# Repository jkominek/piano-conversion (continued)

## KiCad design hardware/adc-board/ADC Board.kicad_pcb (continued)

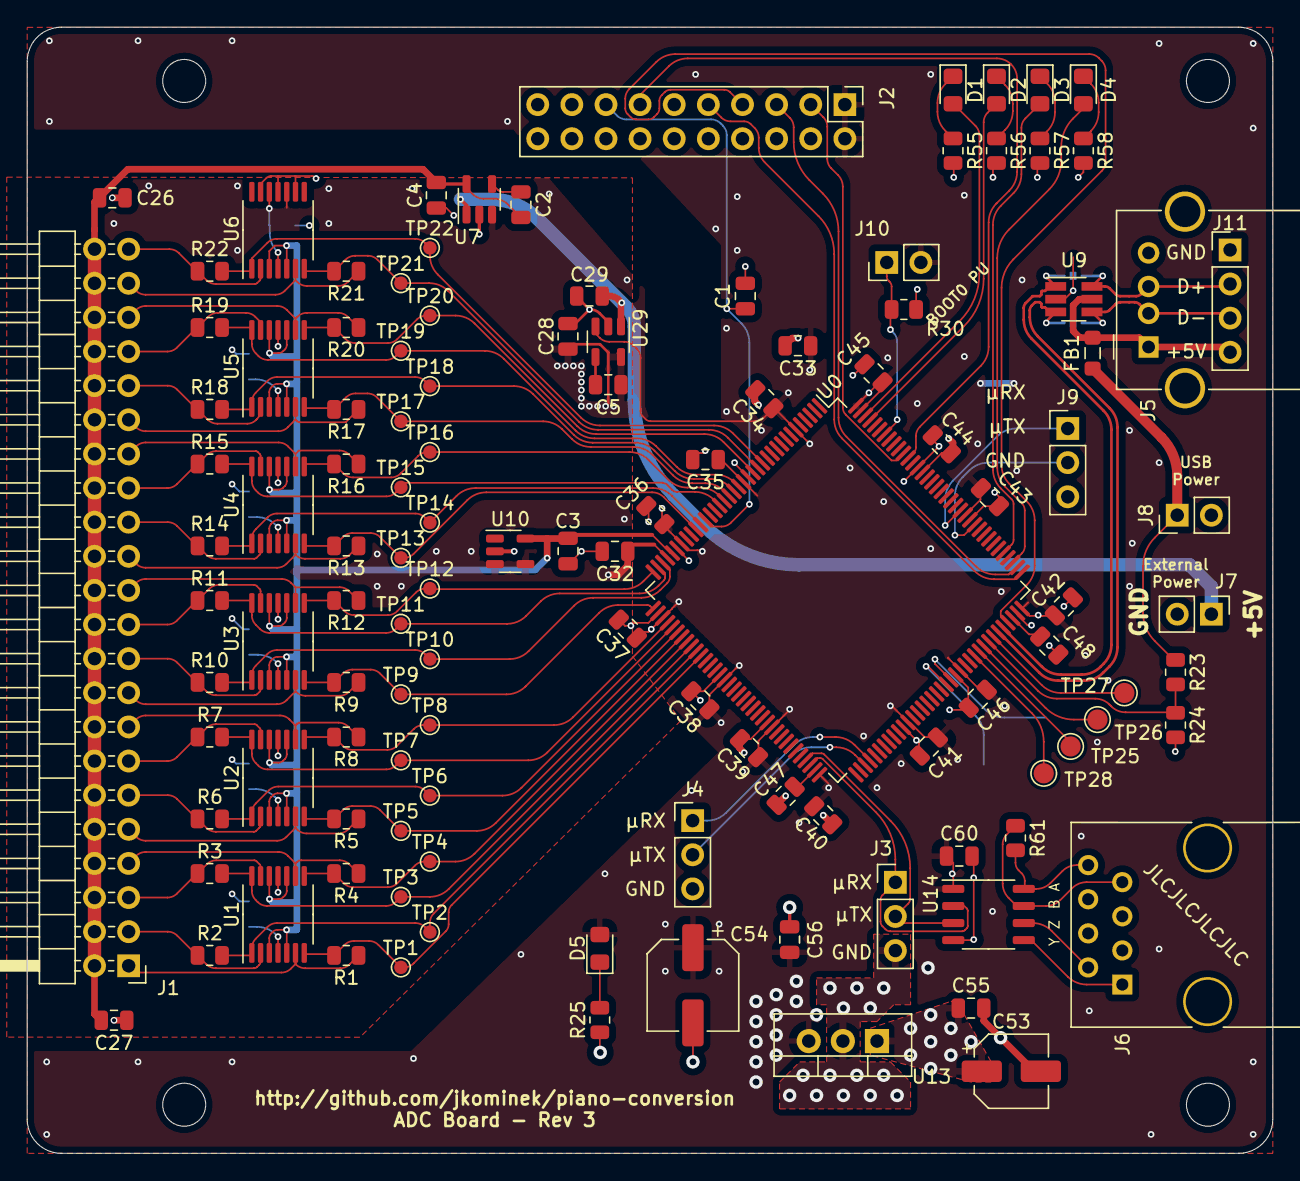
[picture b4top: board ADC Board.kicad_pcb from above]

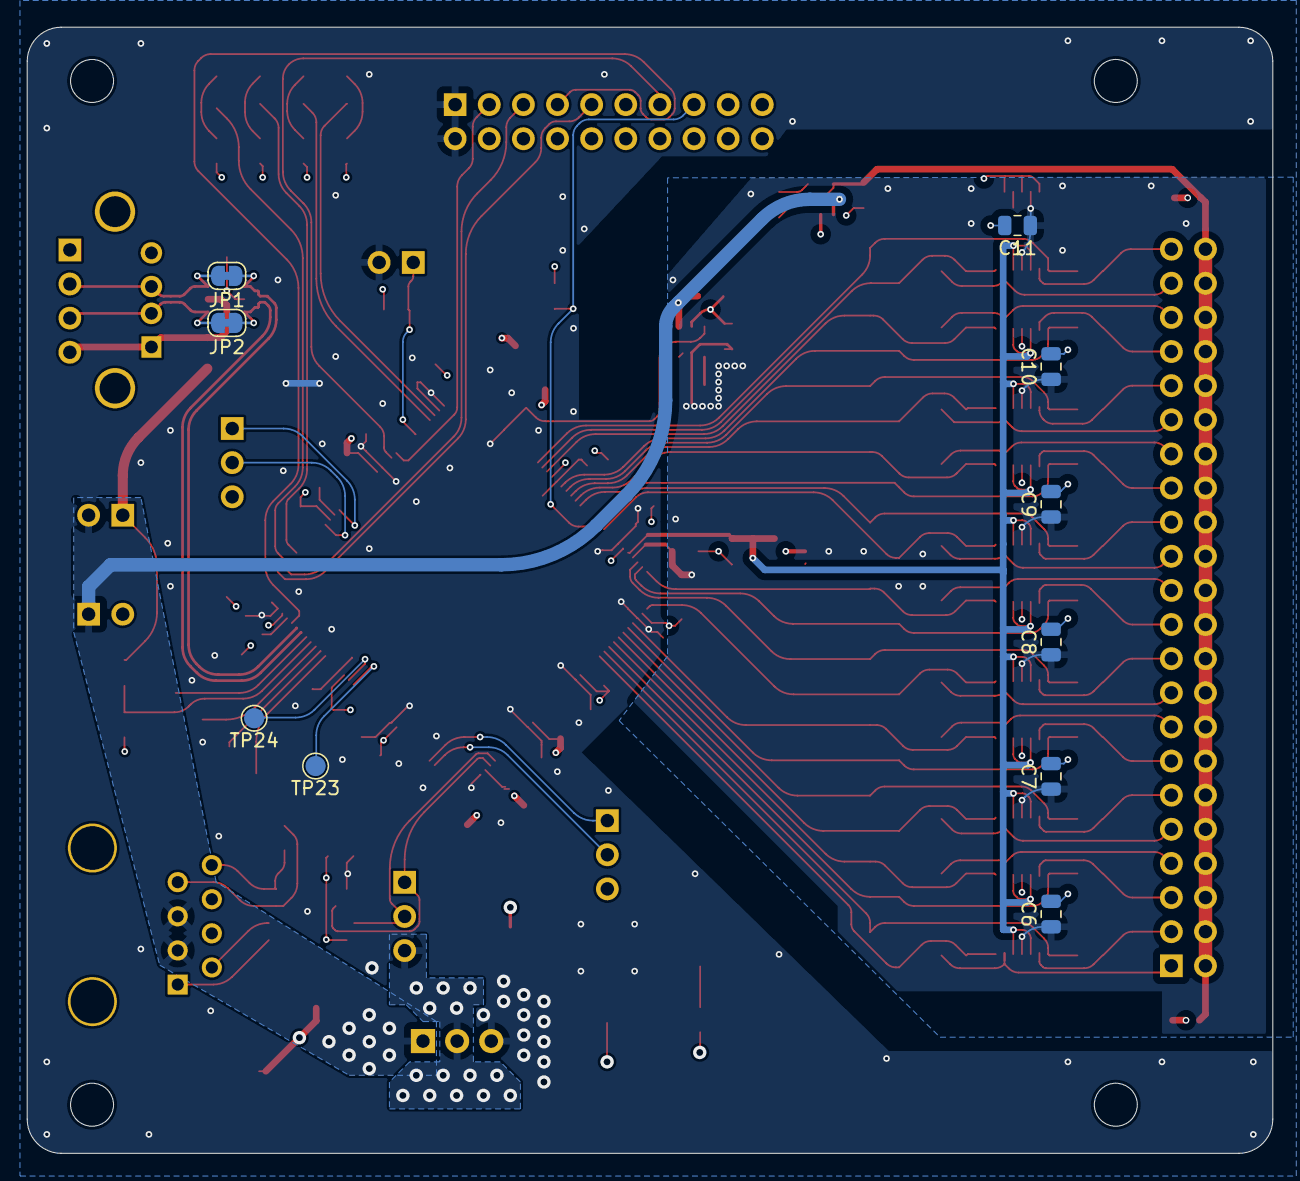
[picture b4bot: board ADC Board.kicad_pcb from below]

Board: 4 copper layers, 92.7 x 83.8 mm, 132 parts (10 on the bottom side), 93 nets.

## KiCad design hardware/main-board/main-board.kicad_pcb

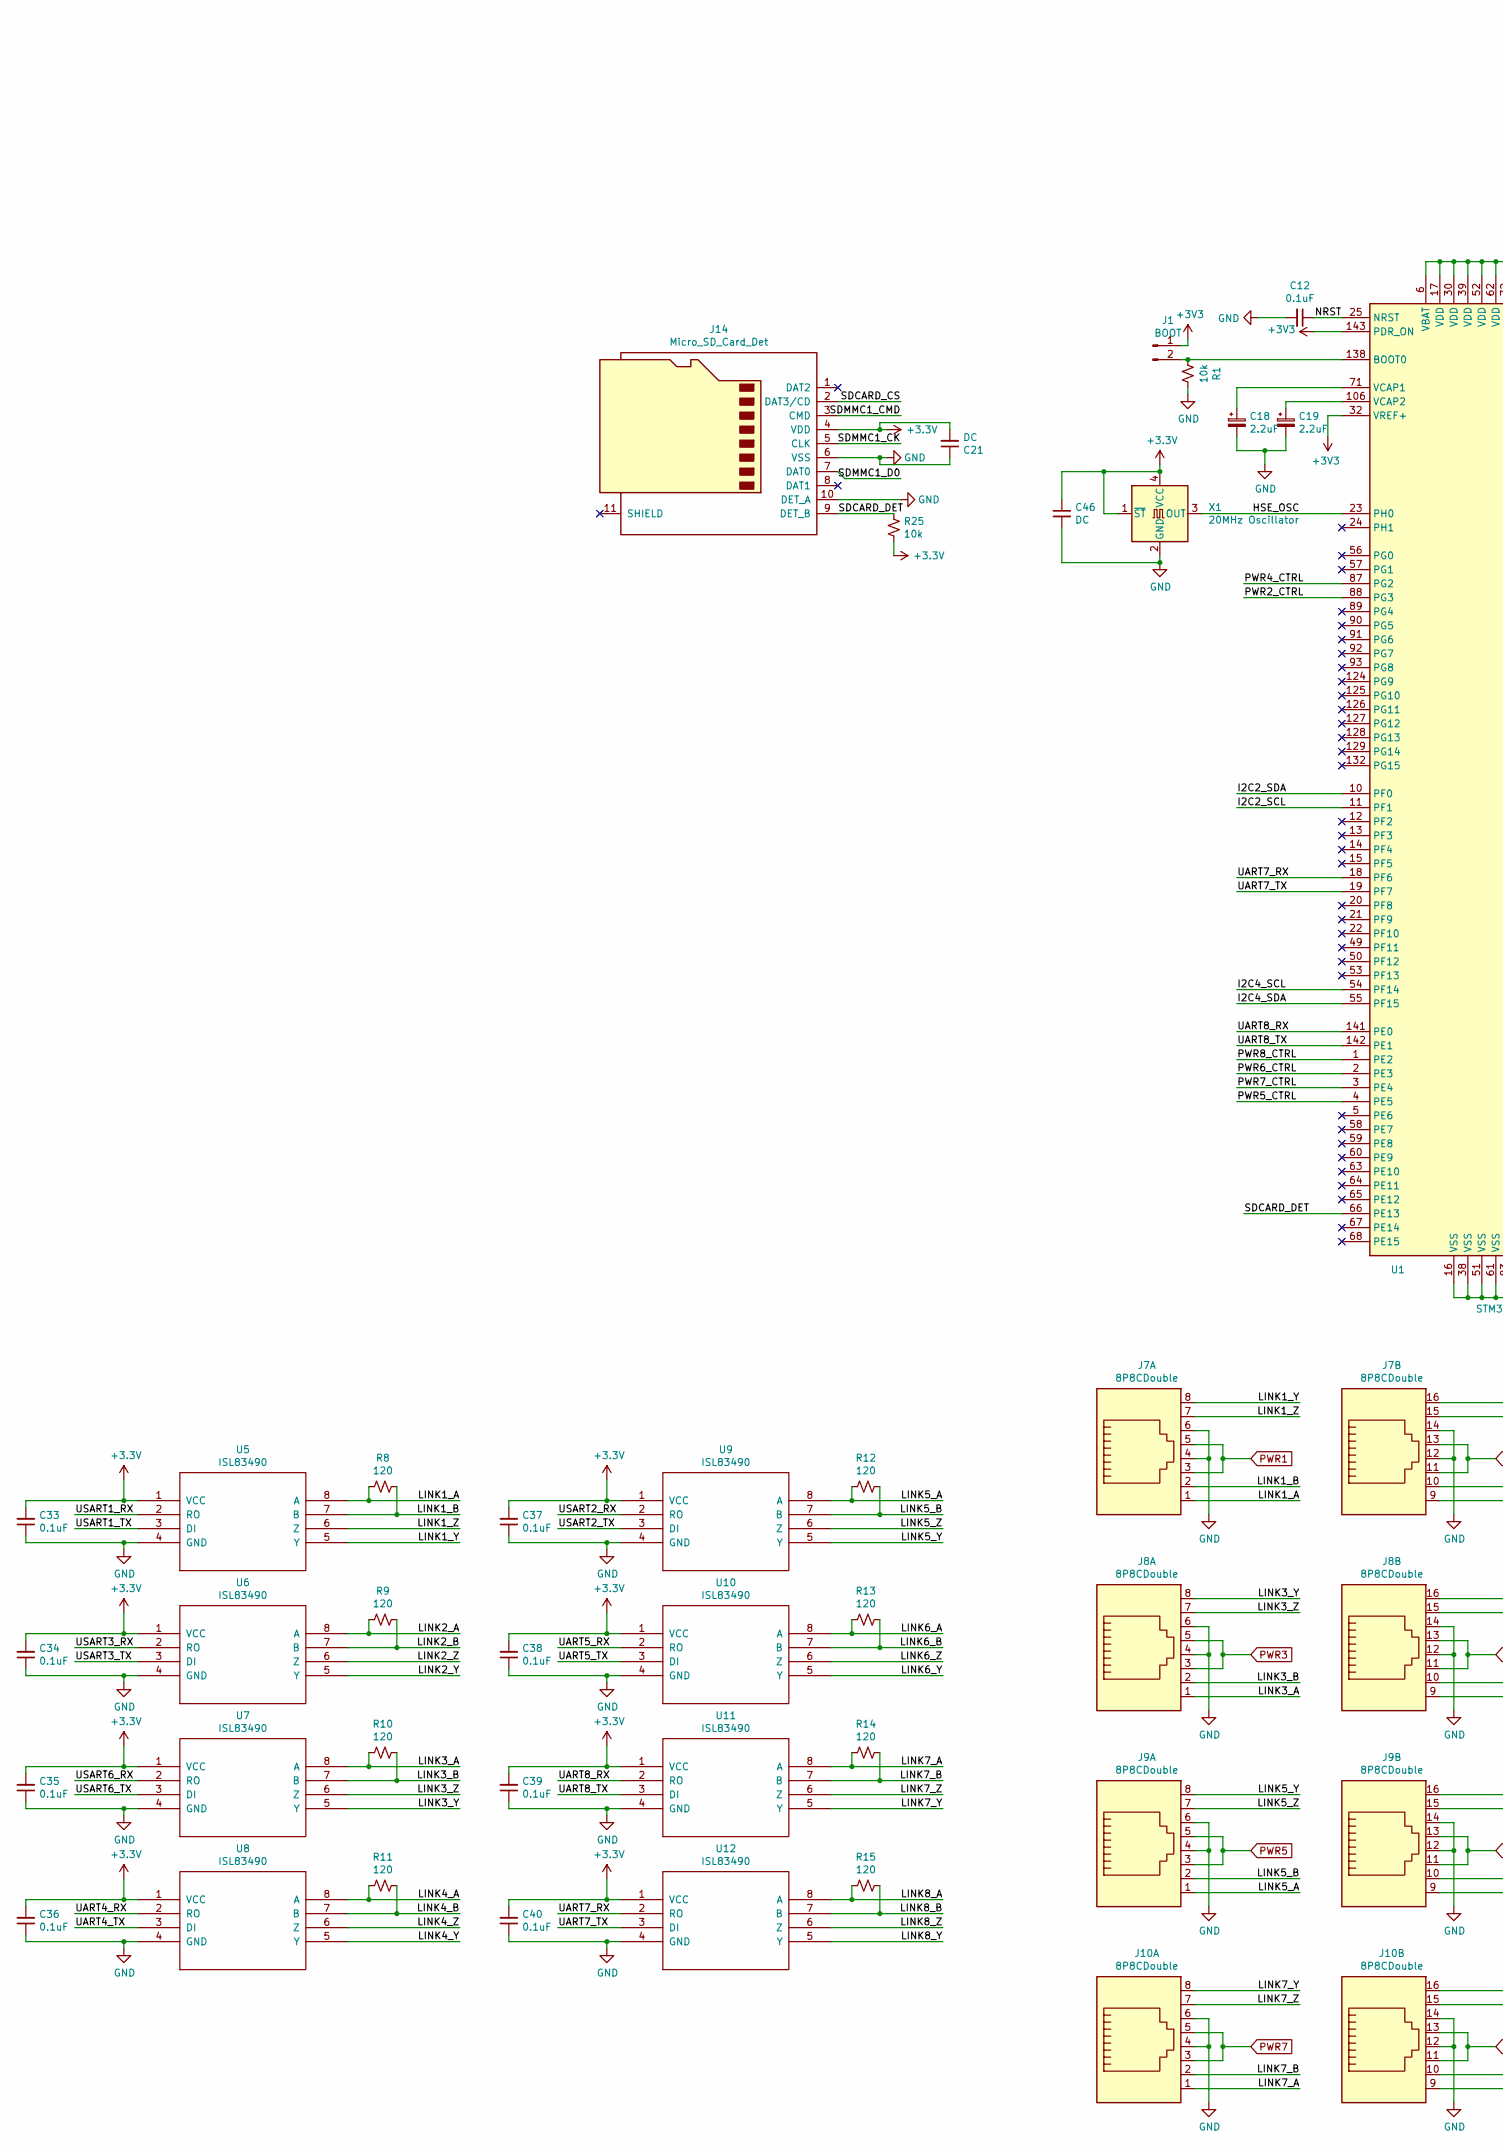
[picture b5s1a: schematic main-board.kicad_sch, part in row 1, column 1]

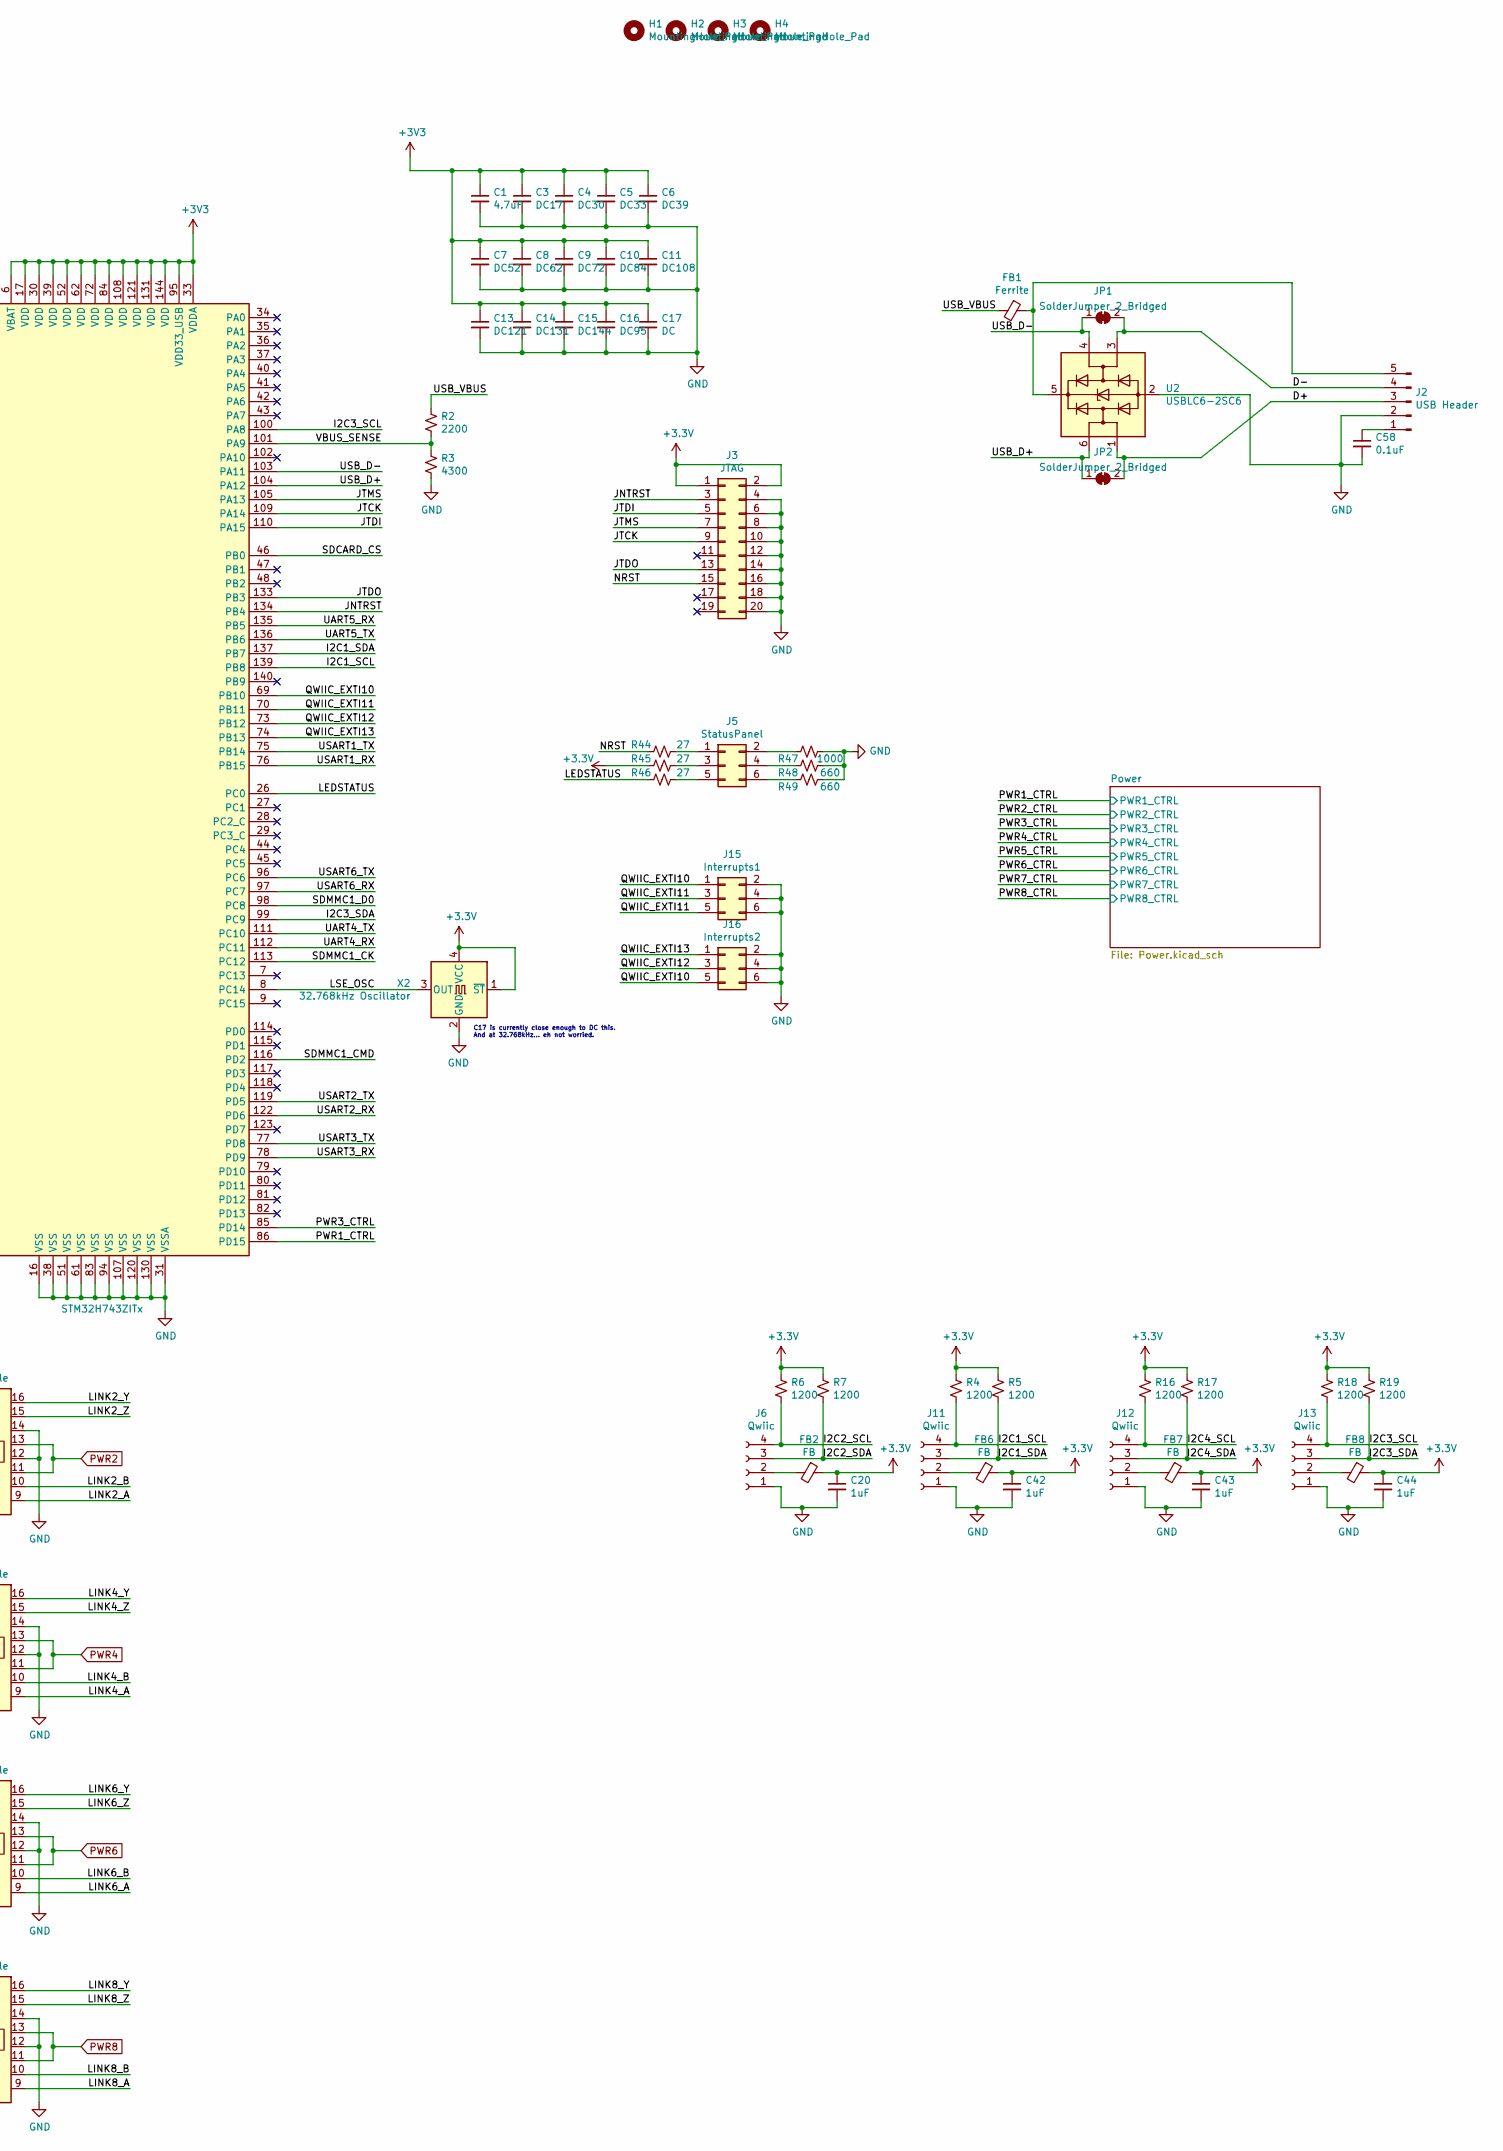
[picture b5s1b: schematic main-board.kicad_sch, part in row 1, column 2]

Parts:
C1: 4.7uF; C_0805_2012Metric
C3: DC17; C_0805_2012Metric
C4: DC30; C_0805_2012Metric
C5: DC33; C_0805_2012Metric
C6: DC39; C_0805_2012Metric
C7: DC52; C_0805_2012Metric
C8: DC62; C_0805_2012Metric
C9: DC72; C_0805_2012Metric
C10: DC84; C_0805_2012Metric
C11: DC108; C_0805_2012Metric
C12, C33, C34, C35, C36, C37, C38, C39, C40, C58: 0.1uF; C_0805_2012Metric
C13: DC121; C_0805_2012Metric
C14: DC131; C_0805_2012Metric
C15: DC144; C_0805_2012Metric
C16: DC95; C_0805_2012Metric
C17, C21, C46: DC; C_0805_2012Metric
C18, C19: 2.2uF; C_0805_2012Metric
C20, C42, C43, C44: 1uF; C_0805_2012Metric
FB1: Ferrite; L_0805_2012Metric_Pad1.05x1.20mm_HandSolder
FB2, FB6, FB7, FB8: FB; L_0805_2012Metric_Pad1.05x1.20mm_HandSolder
H1, H2, H3, H4: MountingHole_Pad; MountingHole_3.2mm_M3
J1: BOOT; Pin_Header_Straight_1x02_Pitch2.54mm
J2: USB Header; Pin_Header_Straight_1x05_Pitch2.54mm
J3: JTAG; Pin_Header_Straight_2x10_Pitch2.54mm
J5: StatusPanel; Pin_Header_Straight_2x03_Pitch2.54mm
J6, J11, J12, J13: Qwiic; JST_SH_SM04B-SRSS-TB_04x1.00mm_Angled
J7, J8, J9, J10: 8P8CDouble; RJ45_DOUBLE
J14: Micro_SD_Card_Det; 114-00841-68
J15: Interrupts1; Pin_Header_Straight_2x03_Pitch2.54mm
J16: Interrupts2; Pin_Header_Straight_2x03_Pitch2.54mm
JP1, JP2: SolderJumper_2_Bridged; SolderJumper-2_P1.3mm_Bridged_RoundedPad1.0x1.5mm
R1, R25: 10k; R_0805
R2: 2200; R_0805
R3: 4300; R_0805
R4, R5, R6, R7, R16, R17, R18, R19: 1200; R_0805
R8, R9, R10, R11, R12, R13, R14, R15: 120; R_0805
R44, R45, R46: 27; R_0805
R47: 1000; R_0805
R48, R49: 660; R_0805
U1: STM32H743ZITx; LQFP-144_20x20mm_Pitch0.5mm
U2: USBLC6-2SC6; SOT-23-6_Handsoldering
U5, U6, U7, U8, U9, U10, U11, U12: ISL83490; SOIC-8_3.9x4.9mm_Pitch1.27mm
X1: 20MHz Oscillator; Oscillator_SMD_SeikoEpson_SG8002CE-4pin_3.2x2.5mm_HandSolde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
X2: 32.768kHz Oscillator; Oscillator_SMD_SeikoEpson_SG8002CE-4pin_3.2x2.5mm_HandSolde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

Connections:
/D+: J2.3, JP2.2 (B), U2.1 (I/O1)
/D-: J2.4, JP1.2 (B), U2.3 (I/O2)
/HSE_OSC: U1.23 (PH0), X1.3 (OUT)
/I2C1_SCL: J11.4, R4.2, U1.139 (PB8)
/I2C1_SDA: J11.3, R5.2, U1.137 (PB7)
/I2C2_SCL: J6.4, R6.2, U1.11 (PF1)
/I2C2_SDA: J6.3, R7.2, U1.10 (PF0)
/I2C3_SCL: J13.4, R18.2, U1.100 (PA8)
/I2C3_SDA: J13.3, R19.2, U1.99 (PC9)
/I2C4_SCL: J12.4, R16.2, U1.54 (PF14)
/I2C4_SDA: J12.3, R17.2, U1.55 (PF15)
/JNTRST: J3.3, U1.134 (PB4)
/JTCK: J3.9, U1.109 (PA14)
/JTDI: J3.5, U1.110 (PA15)
/JTDO: J3.13, U1.133 (PB3)
/JTMS: J3.7, U1.105 (PA13)
/LEDSTATUS: R46.2, U1.26 (PC0)
/LINK1_A: J7.1, R8.2, U5.8 (A)
/LINK1_B: J7.2, R8.1, U5.7 (B)
/LINK1_Y: J7.8, U5.5 (Y)
/LINK1_Z: J7.7, U5.6 (Z)
/LINK2_A: J7.9, R9.2, U6.8 (A)
/LINK2_B: J7.10, R9.1, U6.7 (B)
/LINK2_Y: J7.16, U6.5 (Y)
/LINK2_Z: J7.15, U6.6 (Z)
/LINK3_A: J8.1, R10.2, U7.8 (A)
/LINK3_B: J8.2, R10.1, U7.7 (B)
/LINK3_Y: J8.8, U7.5 (Y)
/LINK3_Z: J8.7, U7.6 (Z)
/LINK4_A: J8.9, R11.2, U8.8 (A)
/LINK4_B: J8.10, R11.1, U8.7 (B)
/LINK4_Y: J8.16, U8.5 (Y)
/LINK4_Z: J8.15, U8.6 (Z)
/LINK5_A: J9.1, R12.2, U9.8 (A)
/LINK5_B: J9.2, R12.1, U9.7 (B)
/LINK5_Y: J9.8, U9.5 (Y)
/LINK5_Z: J9.7, U9.6 (Z)
/LINK6_A: J9.9, R13.2, U10.8 (A)
/LINK6_B: J9.10, R13.1, U10.7 (B)
/LINK6_Y: J9.16, U10.5 (Y)
/LINK6_Z: J9.15, U10.6 (Z)
/LINK7_A: J10.1, R14.2, U11.8 (A)
/LINK7_B: J10.2, R14.1, U11.7 (B)
/LINK7_Y: J10.8, U11.5 (Y)
/LINK7_Z: J10.7, U11.6 (Z)
/LINK8_A: J10.9, R15.2, U12.8 (A)
/LINK8_B: J10.10, R15.1, U12.7 (B)
/LINK8_Y: J10.16, U12.5 (Y)
/LINK8_Z: J10.15, U12.6 (Z)
/LSE_OSC: U1.8 (PC14), X2.3 (OUT)
/NRST: C12.1, J3.15, R44.2, U1.25 (NRST)
/PWR1_CTRL: U1.86 (PD15); also elsewhere on the board
/PWR2_CTRL: U1.88 (PG3); also elsewhere on the board
/PWR3_CTRL: U1.85 (PD14); also elsewhere on the board
/PWR4_CTRL: U1.87 (PG2); also elsewhere on the board
/PWR5_CTRL: U1.4 (PE5); also elsewhere on the board
/PWR6_CTRL: U1.2 (PE3); also elsewhere on the board
/PWR7_CTRL: U1.3 (PE4); also elsewhere on the board
/PWR8_CTRL: U1.1 (PE2); also elsewhere on the board
/QWIIC_EXTI10: J15.1, J16.5, U1.69 (PB10)
/QWIIC_EXTI11: J15.3, J15.5, U1.70 (PB11)
/QWIIC_EXTI12: J16.3, U1.73 (PB12)
/QWIIC_EXTI13: J16.1, U1.74 (PB13)
/SDCARD_CS: J14.2 (DAT3/CD), U1.46 (PB0)
/SDCARD_DET: J14.9 (DET_B), R25.2, U1.66 (PE13)
/SDMMC1_CK: J14.5 (CLK), U1.113 (PC12)
/SDMMC1_CMD: J14.3 (CMD), U1.116 (PD2)
/SDMMC1_D0: J14.7 (DAT0), U1.98 (PC8)
/UART4_RX: U1.112 (PC11), U8.2 (RO)
/UART4_TX: U1.111 (PC10), U8.3 (DI)
/UART5_RX: U1.135 (PB5), U10.2 (RO)
/UART5_TX: U1.136 (PB6), U10.3 (DI)
/UART7_RX: U1.18 (PF6), U12.2 (RO)
/UART7_TX: U1.19 (PF7), U12.3 (DI)
/UART8_RX: U1.141 (PE0), U11.2 (RO)
/UART8_TX: U1.142 (PE1), U11.3 (DI)
/USART1_RX: U1.76 (PB15), U5.2 (RO)
/USART1_TX: U1.75 (PB14), U5.3 (DI)
/USART2_RX: U1.122 (PD6), U9.2 (RO)
/USART2_TX: U1.119 (PD5), U9.3 (DI)
/USART3_RX: U1.78 (PD9), U6.2 (RO)
/USART3_TX: U1.77 (PD8), U6.3 (DI)
/USART6_RX: U1.97 (PC7), U7.2 (RO)
/USART6_TX: U1.96 (PC6), U7.3 (DI)
/USB_D+: JP2.1 (A), U1.104 (PA12), U2.6 (I/O1)
/USB_D-: JP1.1 (A), U1.103 (PA11), U2.4 (I/O2)
/USB_VBUS: FB1.2, R2.1
/VBUS_SENSE: R2.2, R3.1, U1.101 (PA9)
GND: C1.2, C3.2, C4.2, C5.2, C6.2, C7.2, C8.2, C9.2, C10.2, C11.2, C12.2, C13.2, C14.2, C15.2, C16.2, C17.2, C18.2, C19.2, C20.2, C21.1, C33.1, C34.1, C35.1, C36.1, C37.1, C38.1, C39.1, C40.1, C42.2, C43.2, C44.2, C46.2, C58.2, J2.2, J3.4, J3.6, J3.8, J3.10, J3.12, J3.14, J3.16, J3.18, J3.20, J6.1, J7.4, J7.6, J7.12, J7.14, J8.4, J8.6, J8.12, J8.14, J9.4, J9.6, J9.12, J9.14, J10.4, J10.6, J10.12, J10.14, J11.1, J12.1, J13.1, J14.6 (VSS), J14.10 (DET_A), J15.2, J15.4, J15.6, J16.2, J16.4, J16.6, R1.1, R3.2, R47.1, R48.1, R49.1, U1.16 (VSS), U1.31 (VSSA), U1.38 (VSS), U1.51 (VSS), U1.61 (VSS), U1.83 (VSS), U1.94 (VSS), U1.107 (VSS), U1.120 (VSS), U1.130 (VSS), U2.2 (GND), U5.4 (GND), U6.4 (GND), U7.4 (GND), U8.4 (GND), U9.4 (GND), U10.4 (GND), U11.4 (GND), U12.4 (GND), X1.2 (GND), X2.2 (GND); also elsewhere on the board
unnamed: C18.1, U1.71 (VCAP1)
unnamed: C19.1, U1.106 (VCAP2)
unnamed: C58.1, J2.1
unnamed: FB1.1, J2.5, U2.5 (VBUS)
unnamed: FB2.2, J6.2
unnamed: FB6.2, J11.2
unnamed: FB7.2, J12.2
unnamed: FB8.2, J13.2
unnamed: J1.2, R1.2, U1.138 (BOOT0)
unnamed: J5.1, R44.1
unnamed: J5.2, R47.2
unnamed: J5.3, R45.1
unnamed: J5.4, R48.2
unnamed: J5.5, R46.1
unnamed: J5.6, R49.2
PWR1: J7.3, J7.5; also elsewhere on the board
PWR2: J7.11, J7.13; also elsewhere on the board
PWR3: J8.3, J8.5; also elsewhere on the board
PWR4: J8.11, J8.13; also elsewhere on the board
PWR5: J9.3, J9.5; also elsewhere on the board
PWR6: J9.11, J9.13; also elsewhere on the board
PWR7: J10.3, J10.5; also elsewhere on the board
PWR8: J10.11, J10.13; also elsewhere on the board

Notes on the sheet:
C17 is currently close enough to DC this. And at 32.768kHz... eh not worried.

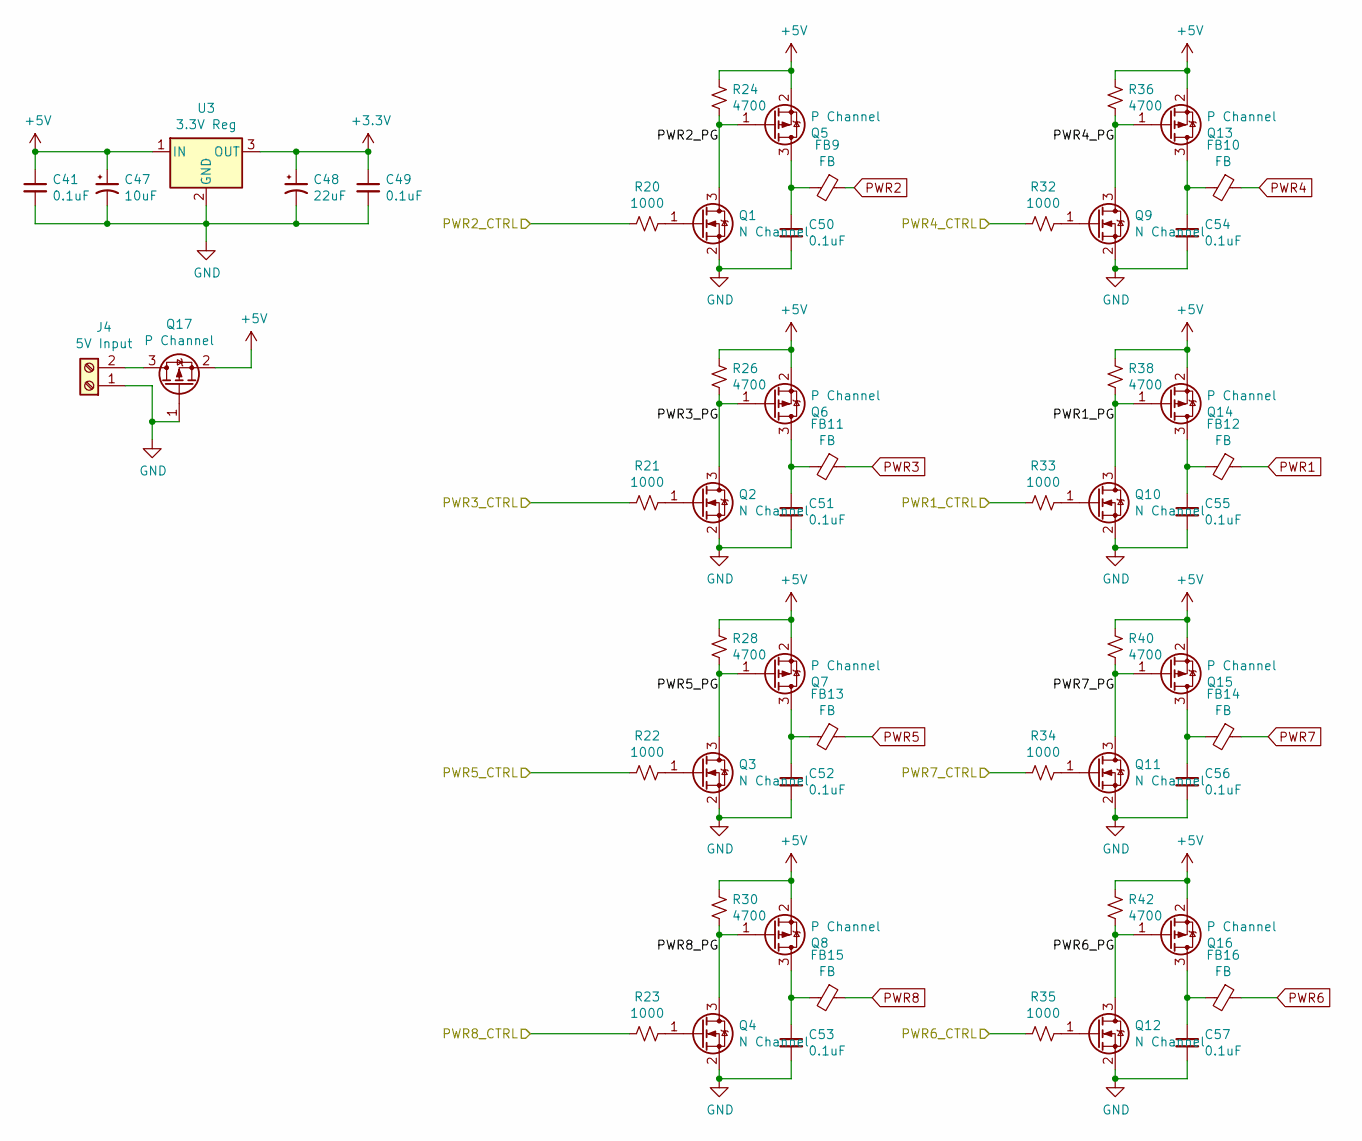
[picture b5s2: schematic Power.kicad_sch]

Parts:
C41, C49, C50, C51, C52, C53, C54, C55, C56, C57: 0.1uF; C_0805_2012Metric
C47: 10uF; CP_Elec_5x5.3
C48: 22uF; CP_Elec_6.3x5.8
FB9, FB10, FB11, FB12, FB13, FB14, FB15, FB16: FB; L_0805_2012Metric_Pad1.05x1.20mm_HandSolder
J4: 5V Input; TerminalBlock_bornier-2_P5.08mm
Q1, Q2, Q3, Q4, Q9, Q10, Q11, Q12: N Channel; SOT-23
Q5, Q6, Q7, Q8, Q13, Q14, Q15, Q16, Q17: P Channel; SOT-23
R20, R21, R22, R23, R32, R33, R34, R35: 1000; R_0805
R24, R26, R28, R30, R36, R38, R40, R42: 4700; R_0805
U3: 3.3V Reg; TO-220-3_Vertical

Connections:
+5V: C41.1, C47.1, Q5.2 (S), Q6.2 (S), Q7.2 (S), Q8.2 (S), Q13.2 (S), Q14.2 (S), Q15.2 (S), Q16.2 (S), Q17.2 (S), R24.1, R26.1, R28.1, R30.1, R36.1, R38.1, R40.1, R42.1, U3.1 (IN)
/PWR1_CTRL: R33.2; also elsewhere on the board
/PWR2_CTRL: R20.2; also elsewhere on the board
/PWR3_CTRL: R21.2; also elsewhere on the board
/PWR4_CTRL: R32.2; also elsewhere on the board
/PWR5_CTRL: R22.2; also elsewhere on the board
/PWR6_CTRL: R35.2; also elsewhere on the board
/PWR7_CTRL: R34.2; also elsewhere on the board
/PWR8_CTRL: R23.2; also elsewhere on the board
/Power/PWR1_PG: Q10.3 (D), Q14.1 (G), R38.2
/Power/PWR2_PG: Q1.3 (D), Q5.1 (G), R24.2
/Power/PWR3_PG: Q2.3 (D), Q6.1 (G), R26.2
/Power/PWR4_PG: Q9.3 (D), Q13.1 (G), R36.2
/Power/PWR5_PG: Q3.3 (D), Q7.1 (G), R28.2
/Power/PWR6_PG: Q12.3 (D), Q16.1 (G), R42.2
/Power/PWR7_PG: Q11.3 (D), Q15.1 (G), R40.2
/Power/PWR8_PG: Q4.3 (D), Q8.1 (G), R30.2
GND: C41.2, C47.2, C48.2, C49.2, C50.2, C51.2, C52.2, C53.2, C54.2, C55.2, C56.2, C57.2, J4.1, Q1.2 (S), Q2.2 (S), Q3.2 (S), Q4.2 (S), Q9.2 (S), Q10.2 (S), Q11.2 (S), Q12.2 (S), Q17.1 (G), U3.2 (GND); also elsewhere on the board
unnamed: C50.1, FB9.2, Q5.3 (D)
unnamed: C51.1, FB11.2, Q6.3 (D)
unnamed: C52.1, FB13.2, Q7.3 (D)
unnamed: C53.1, FB15.2, Q8.3 (D)
unnamed: C54.1, FB10.2, Q13.3 (D)
unnamed: C55.1, FB12.2, Q14.3 (D)
unnamed: C56.1, FB14.2, Q15.3 (D)
unnamed: C57.1, FB16.2, Q16.3 (D)
unnamed: J4.2, Q17.3 (D)
unnamed: Q1.1 (G), R20.1
unnamed: Q2.1 (G), R21.1
unnamed: Q3.1 (G), R22.1
unnamed: Q4.1 (G), R23.1
unnamed: Q9.1 (G), R32.1
unnamed: Q10.1 (G), R33.1
unnamed: Q11.1 (G), R34.1
unnamed: Q12.1 (G), R35.1
PWR1: FB12.1; also elsewhere on the board
PWR2: FB9.1; also elsewhere on the board
PWR3: FB11.1; also elsewhere on the board
PWR4: FB10.1; also elsewhere on the board
PWR5: FB13.1; also elsewhere on the board
PWR6: FB16.1; also elsewhere on the board
PWR7: FB14.1; also elsewhere on the board
PWR8: FB15.1; also elsewhere on the board

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
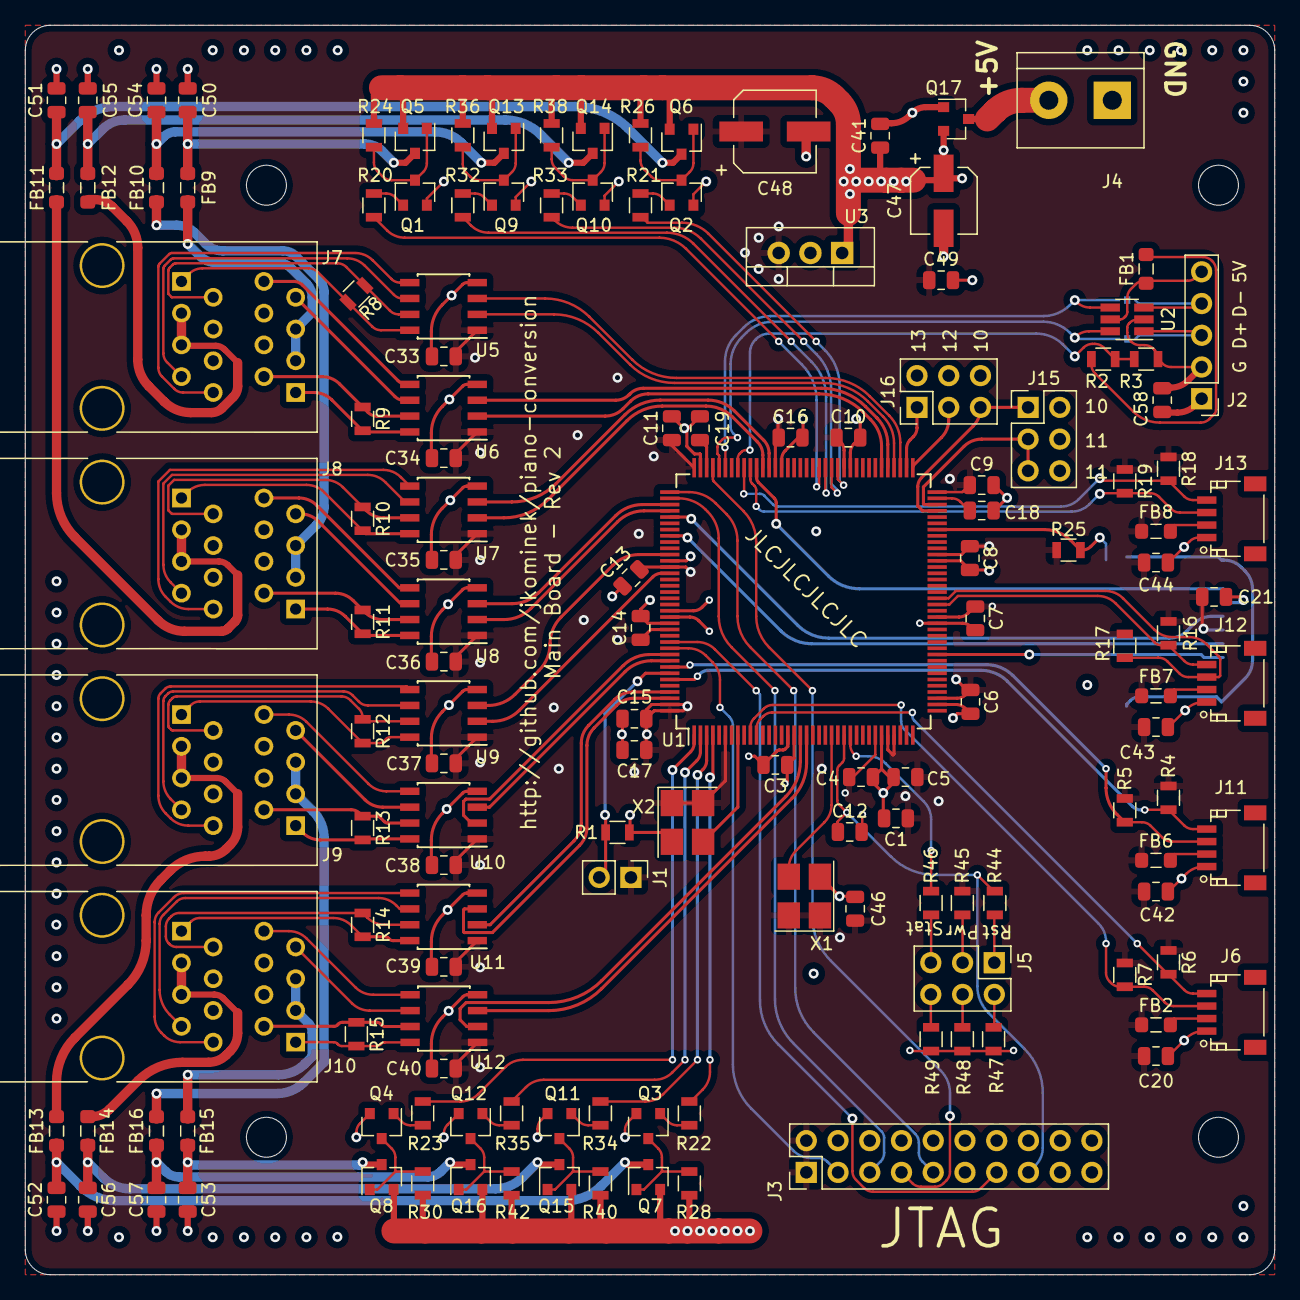
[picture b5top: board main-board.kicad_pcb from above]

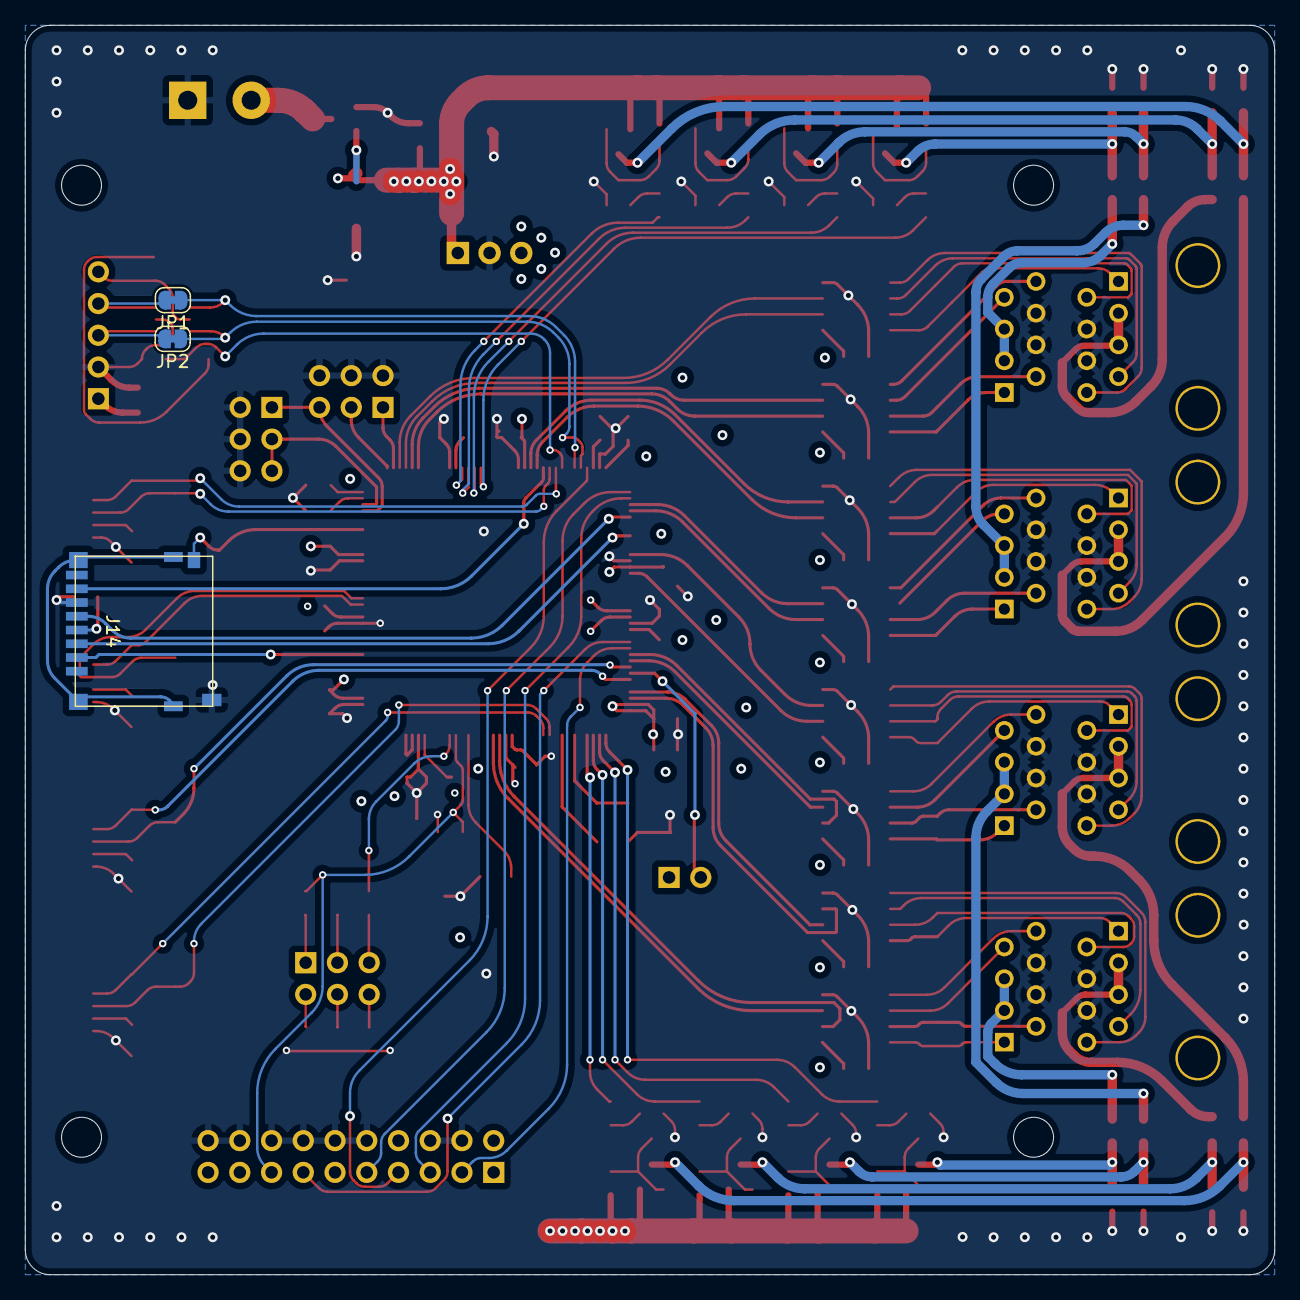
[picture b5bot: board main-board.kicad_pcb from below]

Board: 4 copper layers, 100.0 x 100.0 mm, 152 parts (3 on the bottom side), 139 nets.
